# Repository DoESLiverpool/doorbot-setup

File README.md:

# Setup Doorbot

A set of scripts to set up a DoESLiverpool DoorBot.

## Structure

DoES Liverpool has three types of doorbot.  Most of the basics are shared between them all, and that is all contained within the `base-doorbot` role.  Other roles, such as the one running a web browser for doorbot1, are layered on top of that.

## Steps:

1. Install [Ansible](https://www.ansible.com/get-started) on your computer
1. Using the [Raspberry Pi Imager](https://www.raspberrypi.com/software/) install the latest 32-bit (I think John had trouble with the RFID code on the 64-bit) OS (needs updating for the headless ones, I used the desktop one as it was `doorbot2` that I was fixing, but I think we'd want "Raspberry Pi OS Lite"), and edit the settings to configure:
   * hostname
   * password
   * SSID
   * WiFi password
   * Enable the ssh service (use password authentication)
   (this didn't actually seem to set any of those options when I just tried it, and I had to do them manually with a screen and keyboard when the Pi first booted up)
1. Boot the Raspberry Pi with the micro-SD card, while plugged into a network via Ethernet
1. Find out the IP address of the Raspberry Pi
 * Use nmap (eg: `nmap -p 22 10.0.*.* --open`), router or monitor to find IP address of Pi once booted.
1. Copy your SSH credentials onto the Pi
  ```ssh-copy-id pi@<ip-address-of-the-pi>```
1. Edit the ```./hosts``` file so ansible knows which computer to configure.  Change the IP address in it to match the one you just found out.
1. Check you can run commands on the Pi using Ansible
   ```ansible <doorbotN> -i hosts -a "hostname" -u pi```
1. Create the hashed password file to use in a moment (if you don't already have it). At the prompt, provide the relevant password for the doorbot
   ```mkpasswd --method=sha-512 > protected_scripts/doorbot1-pwd.txt```
1. Change the SSH port and default password on the doorbot
   ```ansible-playbook ssh-config-doorbot1.yml -e pi_password=`cat protected_scripts/doorbot1-pwd.txt` -i hosts```
1. Populate `protected_scripts/id_ed25519` and `protected_scripts/id_ed25519.pub`, most likely by copying contents from an existing doorbot.
1. Update the Pi, using the correct playbook for the doorbot you're creating, e.g.
   ```ansible-playbook doorbot1.yml -i hosts```

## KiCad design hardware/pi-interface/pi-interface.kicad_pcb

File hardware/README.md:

# Hardware

The non-software parts of a Doorbot.  

## pi-interface

KiCad project to define the PCB to interface from a Raspberry Pi to the SL030 RFID reader and a 12V door striker solenoid.  Takes power from a standard PC hard drive power connector.

Requires a number of additional parts libraries:

 * https://github.com/KiCad/kicad-library
 * http://www.smisioto.eu/elettronica/kicad

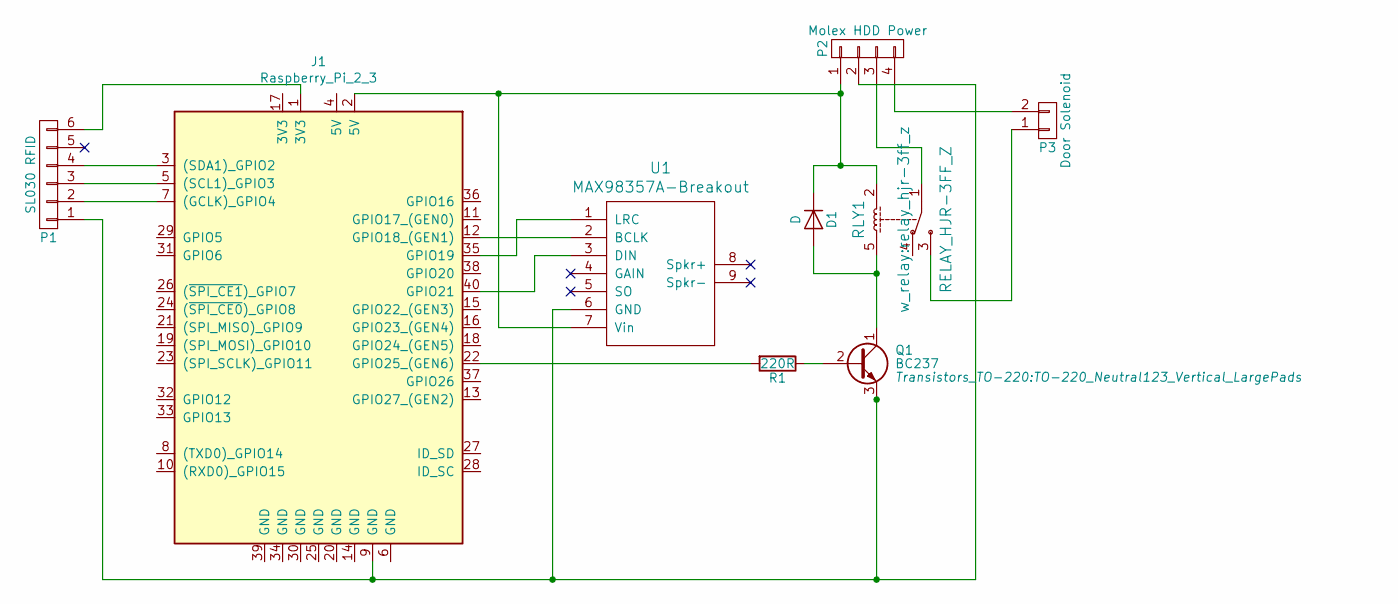
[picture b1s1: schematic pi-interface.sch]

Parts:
D1: D; Diode_DO-201AD_Horizontal_RM15
J1: Raspberry_Pi_2_3; Pin_Header_Straight_2x20
P1: SL030 RFID; Pin_Header_Angled_1x06
P2: Molex HDD Power; mstbva_2,5%2f4-g-5,08; Farnell Part 148086
P3: Door Solenoid; mstba_2,5%2f2-g-5,08; Farnell Part 2396251
Q1: BC237; TO-220_Neutral123_Vertical_LargePads
R1: 220R; Resistor_Horizontal_RM10mm
RLY1: RELAY_HJR-3FF_Z; relay_hjr-3ff_z; Farnell Part 2325631
U1: MAX98357A-Breakout; MAX98357-Breakout

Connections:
unnamed: D1.1 (K), J1.2 (5V), P2.1, RLY1.2, U1.7 (Vin)
unnamed: D1.2 (A), Q1.1 (C), RLY1.5
unnamed: J1.1 (3V3), P1.6
unnamed: J1.3 ((SDA1)_GPIO2), P1.4
unnamed: J1.5 ((SCL1)_GPIO3), P1.3
unnamed: J1.7 ((GCLK)_GPIO4), P1.2
unnamed: J1.9 (GND), P1.1, P2.2, Q1.3 (E), U1.6 (GND)
unnamed: J1.12 (GPIO18_(GEN1)), U1.2 (BCLK)
unnamed: J1.22 (GPIO25_(GEN6)), R1.2
unnamed: J1.35 (GPIO19), U1.1 (LRC)
unnamed: J1.40 (GPIO21), U1.3 (DIN)
unnamed: P2.3, RLY1.1
unnamed: P2.4, P3.2
unnamed: P3.1, RLY1.3
unnamed: Q1.2 (B), R1.1

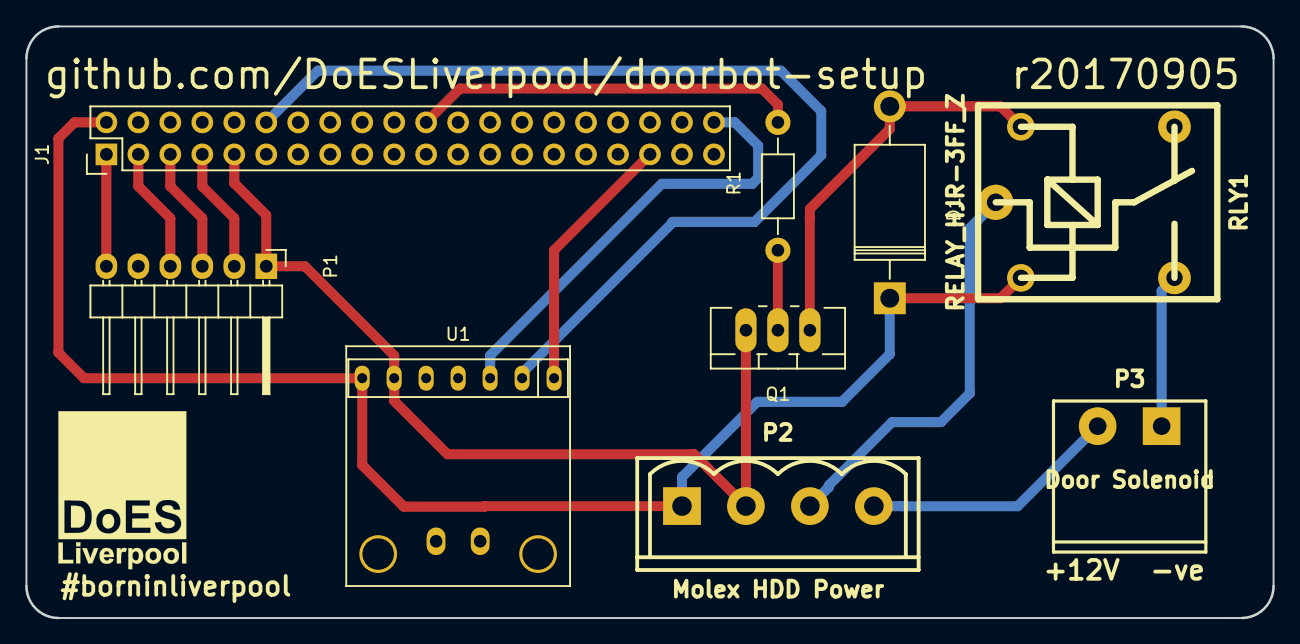
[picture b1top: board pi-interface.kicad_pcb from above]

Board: 2 copper layers, 99.1 x 47.0 mm, 9 parts (0 on the bottom side), 15 nets.

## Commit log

2014-07-04 Initial scripts for setting up SSH.
2014-07-04 Wi-Fi setup
2014-07-04 Fixing SSH setup script.
2014-07-04 Actually edit the rc.local, fix string comparison
2014-07-04 Fix string comparison
2014-07-04 Initial local setup, moved into single script.
2014-07-04 Removing old files.
2014-07-04 Fixing comparison bug, better allowing multiple runs.
2014-07-04 Actually edit the interfaces file for wifi.
2014-07-04 Initial setup fixes.
2014-07-04 Fixes.
2014-07-04 Remote setup can change the SSH port.
2014-07-04 Deploy script for log cards on a doorbot.
2014-07-15 Updating readme with more instructions.
2014-08-15 I suspect we should just add the i2c module to the ones loaded, rather than replace any already being loaded with i2c.
    I haven't tested this yet, mind.
2015-06-13 Now copies the Raspbian image onto the SD card at the start of the script
2015-06-13 Fixed "smart-dash" in command parameters and changed port to the one which SSH will be listening on at the time you run it
2015-06-13 Added missing > (so it doesn't look like you redirect input to the script :-)
2015-06-14 Added known host details for bitbucket so the git clone won't fail
2015-06-14 Now installs prerequisites and configures doesscreens if the config requires it. Fixes #3. Also uses KWeb3 as the browser in that case, which fixes #4
2015-06-16 Added instruction to expand the filesystem to fill the SD card
2015-06-16 Added the config reload scripts and ssh config to the setup
2015-09-06 A start on a PCB for the Raspberry Pi/RFID/door interface.
2015-09-07 Improved PCB, still needs checking against parts ordered
2015-09-10 First finished (fingers crossed) PCB design.
2016-11-29 Add original design notes (found on the old Wiki when it was being decommissioned)
2017-01-23 Set up initial Ansible framework.
2017-02-02 Migrated doorbot1 set up to ansible.
2017-02-02 Set the volume to max
2017-02-02 Turn off the screensaver
2017-02-02 Change the default passwords on doorbots 2 and 3
2017-02-02 Disable the screensaver from the main X setup
2017-02-02 Playbook to build a doorbot2 (with I2S DAC)
2017-02-02 Add playbook for doorbot3
2017-02-03 Tweaks so the deploy new RFID tags script works
2017-02-03 Seemingly the key step to stop the screen going blank after a while
2017-02-06 Add playbook to build the RFID reader code from scratch
2017-02-06 Clear out files from old way of provisioning
2017-08-16 I2S DAC added to PCB. Fixes #17
    Also added DoES Liverpool logo to silkscreen, and other mods for the first revision of the PCB sent to be manufactured.
2017-08-16 Panelized version and r20170815 Gerbers sent to production.
2017-09-05 Enlarge holes for the Molex connector. Fixes #21
2017-09-05 Add Farnell part numbers for more of the components. Part of #6
2018-12-17 Separate out the web browser tasks to a screen role and add that role to doorbots 1 and 2, tweaked the SSH documentation in README.md
2019-01-28 Switch the repo we use for doorbots-config and also add doorbots 4 & 5 to the ssh config
2019-05-21 Make sure the install on a fresh pi works, including screen. Update README
2019-06-07 Add open-door.sh to repo and ansible scripts. Fixes #26
2023-04-05 Save Ansible scripts for doorbots 4 and 5
2024-09-28 # If applied this commit will... Make some improvements to make the setup more realiable
    Disables the screen role for doorbot2 as it relies on a kweb browser that's unavailable and the screen isn't used anyway.
    Updates the git repo references to be modern
    Moves the SSH key tasks earlier in the deploy
2025-12-08 Updates for Trixie version of the OS. Fixes #28
2025-12-11 Add I2C driver overlay so we don't get failures of the RFID app. Fixes #31
2025-12-12 Move to newer ed25519 ssh keys. Fixes #32
